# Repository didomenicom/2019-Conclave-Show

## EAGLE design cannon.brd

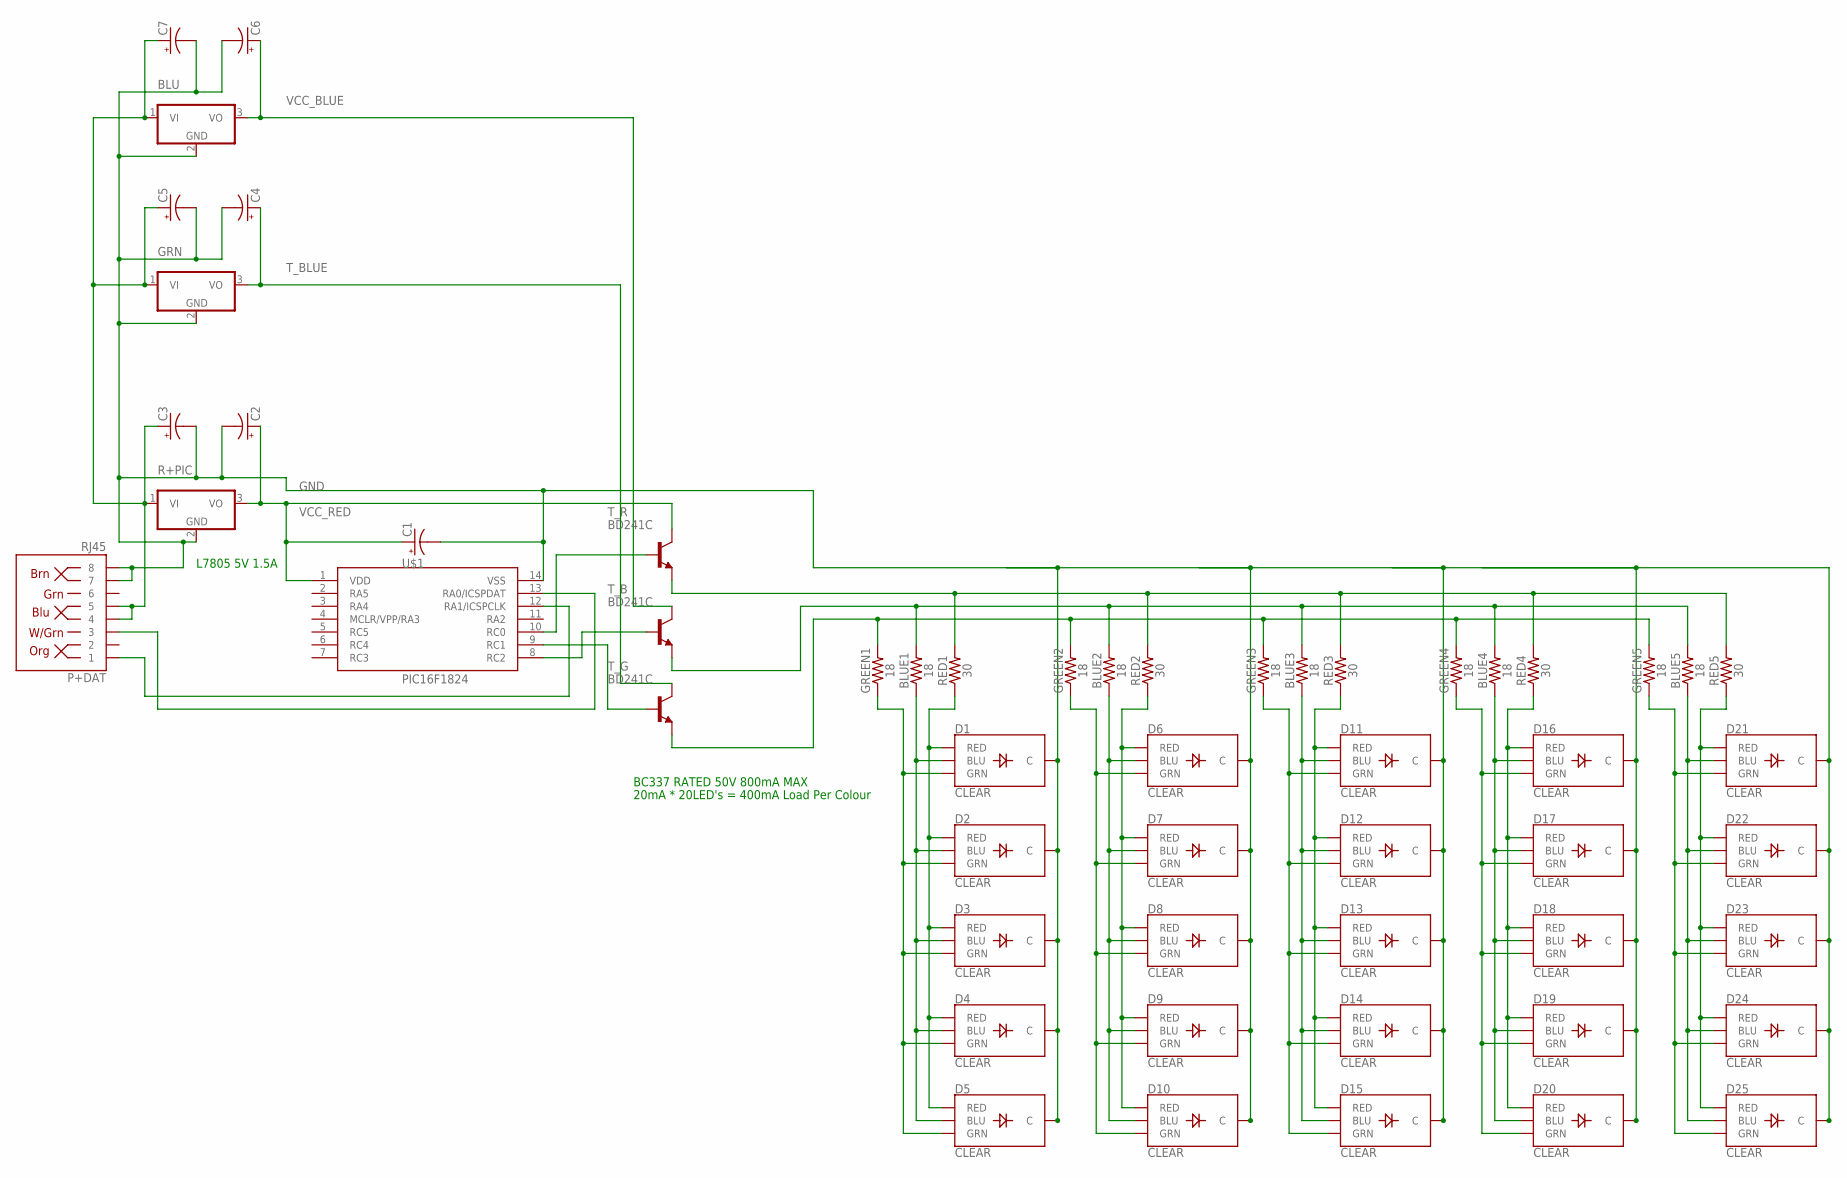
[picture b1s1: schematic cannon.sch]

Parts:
BLU: 7805TV; TO220V
BLUE1, BLUE2, BLUE3, BLUE4, BLUE5: 18; AXIAL-0.3
C1, C2, C4, C6: 0.1uF; E2,5-6
C3, C5, C7: 0.33uF; E2,5-6
D1, D2, D3, D4, D5, D6, D7, D8, D9, D10, D11, D12, D13, D14, D15, D16, D17, D18, D19, D20, D21, D22, D23, D24, D25: CLEAR; LED-RGB-THRU
GREEN1, GREEN2, GREEN3, GREEN4, GREEN5: 18; AXIAL-0.3
GRN: 7805TV; TO220V
P+DAT: RJ45; RJ45-8
R+PIC: 7805TV; TO220V
RED1, RED2, RED3, RED4, RED5: 30; AXIAL-0.3
T_B: BD241C; TO220BV
T_G: BD241C; TO220BV
T_R: BD241C; TO220BV
U$1: PIC16F1824; DIP787W45P254L1905H533Q14B

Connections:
GND: BLU.2 (GND), C1.-, C2.-, C3.-, C4.-, C5.-, C6.-, C7.-, D1.2 (C), D2.2 (C), D3.2 (C), D4.2 (C), D5.2 (C), D6.2 (C), D7.2 (C), D8.2 (C), D9.2 (C), D10.2 (C), D11.2 (C), D12.2 (C), D13.2 (C), D14.2 (C), D15.2 (C), D16.2 (C), D17.2 (C), D18.2 (C), D19.2 (C), D20.2 (C), D21.2 (C), D22.2 (C), D23.2 (C), D24.2 (C), D25.2 (C), GRN.2 (GND), P+DAT.7, P+DAT.8, R+PIC.2 (GND), U$1.14 (VSS)
unnamed: P+DAT.1, U$1.12 (RA1/ICSPCLK)
unnamed: P+DAT.3, U$1.13 (RA0/ICSPDAT)
unnamed: RED1.P$2 (2), RED2.P$2 (2), RED3.P$2 (2), RED4.P$2 (2), RED5.P$2 (2), T_R.3 (E)
unnamed: T_R.1 (B), U$1.10 (RC0)
unnamed: T_G.1 (B), U$1.9 (RC1)
unnamed: T_B.1 (B), U$1.8 (RC2)
unnamed: D1.1 (RED), D2.1 (RED), D3.1 (RED), D4.1 (RED), D5.1 (RED), RED1.P$1 (1)
unnamed: BLUE2.P$1 (1), D6.4 (BLU), D7.4 (BLU), D8.4 (BLU), D9.4 (BLU), D10.4 (BLU)
unnamed: D6.1 (RED), D7.1 (RED), D8.1 (RED), D9.1 (RED), D10.1 (RED), RED2.P$1 (1)
unnamed: D6.3 (GRN), D7.3 (GRN), D8.3 (GRN), D9.3 (GRN), D10.3 (GRN), GREEN2.P$1 (1)
unnamed: BLUE1.P$1 (1), D1.4 (BLU), D2.4 (BLU), D3.4 (BLU), D4.4 (BLU), D5.4 (BLU)
unnamed: D1.3 (GRN), D2.3 (GRN), D3.3 (GRN), D4.3 (GRN), D5.3 (GRN), GREEN1.P$1 (1)
unnamed: D11.3 (GRN), D12.3 (GRN), D13.3 (GRN), D14.3 (GRN), D15.3 (GRN), GREEN3.P$1 (1)
unnamed: BLUE3.P$1 (1), D11.4 (BLU), D12.4 (BLU), D13.4 (BLU), D14.4 (BLU), D15.4 (BLU)
unnamed: BLUE1.P$2 (2), BLUE2.P$2 (2), BLUE3.P$2 (2), BLUE4.P$2 (2), BLUE5.P$2 (2), T_B.3 (E)
unnamed: D11.1 (RED), D12.1 (RED), D13.1 (RED), D14.1 (RED), D15.1 (RED), RED3.P$1 (1)
unnamed: D16.3 (GRN), D17.3 (GRN), D18.3 (GRN), D19.3 (GRN), D20.3 (GRN), GREEN4.P$1 (1)
unnamed: BLUE4.P$1 (1), D16.4 (BLU), D17.4 (BLU), D18.4 (BLU), D19.4 (BLU), D20.4 (BLU)
unnamed: D16.1 (RED), D17.1 (RED), D18.1 (RED), D19.1 (RED), D20.1 (RED), RED4.P$1 (1)
unnamed: GREEN1.P$2 (2), GREEN2.P$2 (2), GREEN3.P$2 (2), GREEN4.P$2 (2), GREEN5.P$2 (2), T_G.3 (E)
unnamed: BLU.1 (VI), C3.+, C5.+, C7.+, GRN.1 (VI), P+DAT.4, P+DAT.5, R+PIC.1 (VI)
unnamed: D21.3 (GRN), D22.3 (GRN), D23.3 (GRN), D24.3 (GRN), D25.3 (GRN), GREEN5.P$1 (1)
unnamed: BLUE5.P$1 (1), D21.4 (BLU), D22.4 (BLU), D23.4 (BLU), D24.4 (BLU), D25.4 (BLU)
unnamed: D21.1 (RED), D22.1 (RED), D23.1 (RED), D24.1 (RED), D25.1 (RED), RED5.P$1 (1)
T_BLUE: C4.+, GRN.3 (VO), T_G.2 (C)
VCC_BLUE: BLU.3 (VO), C6.+, T_B.2 (C)
VCC_RED: C1.+, C2.+, R+PIC.3 (VO), T_R.2 (C), U$1.1 (VDD)

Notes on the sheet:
BC337 RATED 50V 800mA MAX
20mA * 20LED's = 400mA Load Per Colour
L7805 5V 1.5A

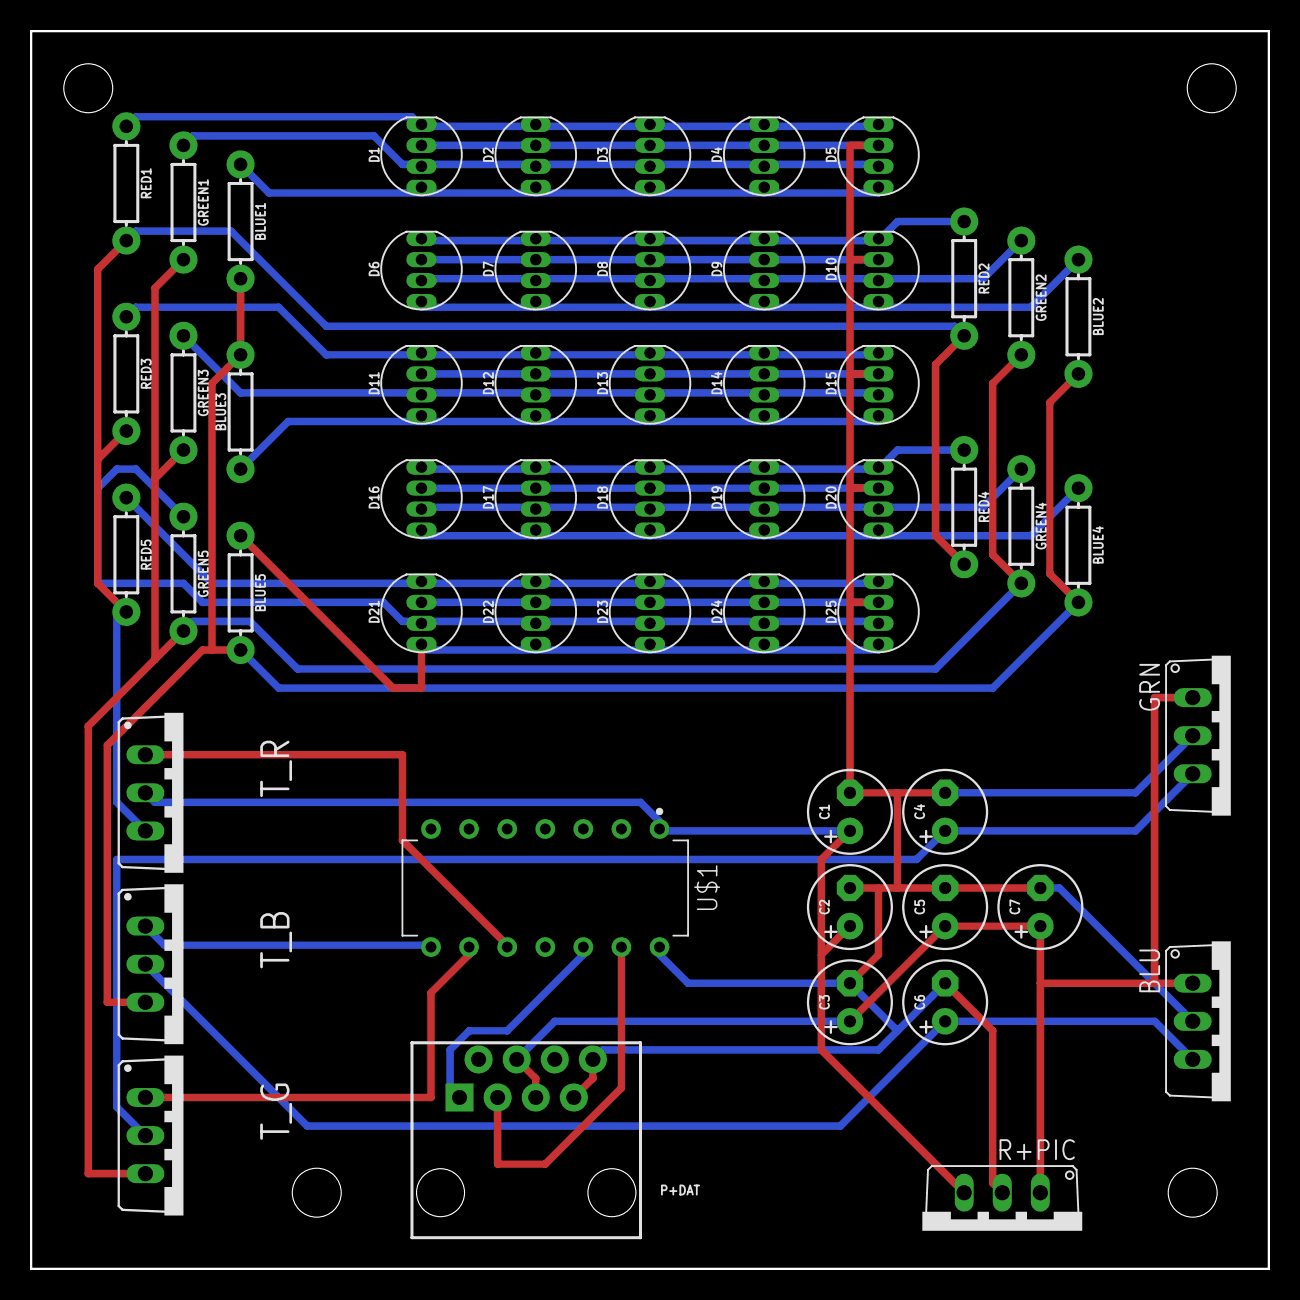
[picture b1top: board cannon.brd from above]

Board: 2 copper layers, 82.5 x 82.5 mm, 55 parts (0 on the bottom side), 28 nets.

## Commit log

2019-03-06 First version of the LED board
2019-04-12 Updated Board, Removed In Circuit programming
    Adjusted RJ45 pins for POE standard BOARD DESIGN NOT CHANGED!!! DO NOT USE TO MAKE BOARDS
2019-04-14 Updated everything
    Updated capacitor size, transistor pad, power reg pad, and LED pad
2019-04-18 Modified traces and holes
2019-04-21 Adding bigger mount holes
2019-04-21 Moved power inwards for heat sinks

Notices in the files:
parts and their libraries:
SparkFun-Resistors: Licensing: Creative Commons ShareAlike 4.0 International - https://creativecommons.org/licenses/by-sa/4.0
